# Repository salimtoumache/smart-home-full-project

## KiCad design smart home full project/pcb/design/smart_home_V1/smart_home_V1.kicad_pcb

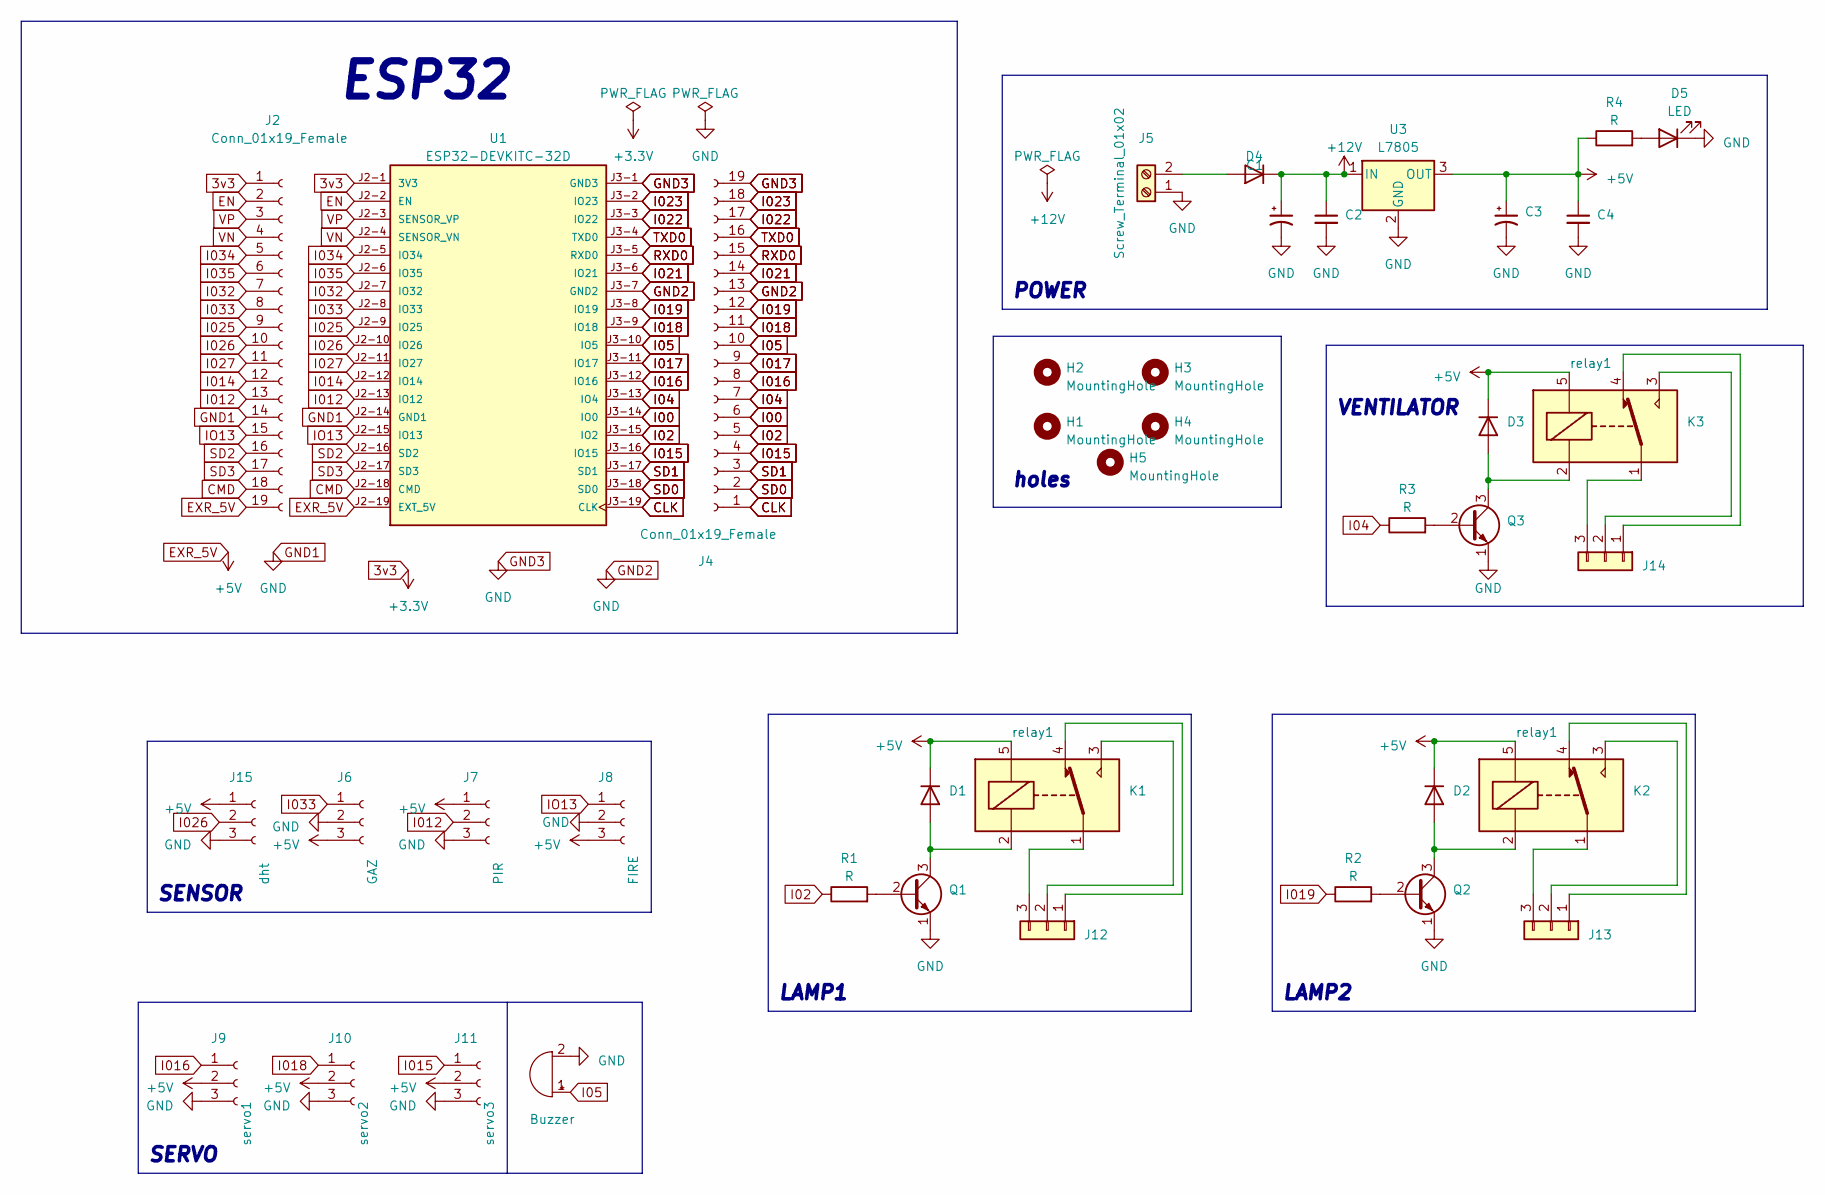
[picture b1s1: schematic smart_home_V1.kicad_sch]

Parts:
BZ1: Buzzer; MagneticBuzzer_ProSignal_ABI-010-RC
C1, C3: C_Polarized_Small_US; CP_Radial_D8.0mm_P3.50mm
C2, C4: C_Small; C_Disc_D4.7mm_W2.5mm_P5.00mm
D1, D2, D3, D4: 1N4448; D_DO-35_SOD27_P7.62mm_Horizontal
D5: LED; LED_D4.0mm
H1, H2, H3, H4, H5: MountingHole; MountingHole_2.5mm_Pad_TopBottom
J2, J4: Conn_01x19_Female; PinHeader_1x19_P2.00mm_Vertical
J5: Screw_Terminal_01x02; TerminalBlock_Phoenix_MKDS-1,5-2_1x02_P5.00mm_Horizontal
J6: GAZ; PinSocket_1x03_P2.54mm_Vertical
J7: PIR; PinSocket_1x03_P2.54mm_Vertical
J8: FIRE; PinSocket_1x03_P2.54mm_Vertical
J9: servo1; PinHeader_1x03_P2.54mm_Vertical
J10: servo2; PinHeader_1x03_P2.54mm_Vertical
J11: servo3; PinHeader_1x03_P2.54mm_Vertical
J12, J13, J14: Conn_01x03; TerminalBlock_Phoenix_MKDS-1,5-3-5.08_1x03_P5.08mm_Horizont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
J15: dht; PinSocket_1x03_P2.54mm_Vertical
K1, K2, K3: relay1; Relay_SPDT_SANYOU_SRD_Series_Form_C
Q1, Q2, Q3: 2N3904; TO-92_Inline
R1, R2, R3, R4: R; R_Axial_DIN0207_L6.3mm_D2.5mm_P7.62mm_Horizontal
U1: ESP32-DEVKITC-32D; MODULE_ESP32-DEVKITC-32D; PARTREV V4
U3: L7805; TO-220-3_Vertical

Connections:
3v3: J2.1, U1.J2-1 (3V3)
+12V: C1.1, C2.1, D4.1 (K), U3.1 (IN)
CLK: J4.1, U1.J3-19 (CLK)
CMD: J2.18, U1.J2-18 (CMD)
EN: J2.2, U1.J2-2 (EN)
EXR_5V: C3.1, C4.1, D1.1 (K), D2.1 (K), D3.1 (K), J2.19, J6.3, J7.1, J8.3, J9.2, J10.2, J11.2, J15.1, K1.5, K2.5, K3.5, R4.1, U1.J2-19 (EXT_5V), U3.3 (OUT)
GND1: BZ1.2 (+), C1.2, C2.2, C3.2, C4.2, D5.1 (K), J2.14, J4.13, J4.19, J5.1, J6.2, J7.3, J8.2, J9.3, J10.3, J11.3, J15.3, Q1.1 (E), Q2.1 (E), Q3.1 (E), U1.J2-14 (GND1), U1.J3-1 (GND3), U1.J3-7 (GND2), U3.2 (GND)
I00: J4.6, U1.J3-14 (IO0)
I02: J4.5, R1.1, U1.J3-15 (IO2)
I04: J4.7, R3.1, U1.J3-13 (IO4)
I05: BZ1.1 (-), J4.10, U1.J3-10 (IO5)
I012: J2.13, J7.2, U1.J2-13 (IO12)
I014: J2.12, U1.J2-12 (IO14)
I015: J4.4, J11.1, U1.J3-16 (IO15)
I016: J4.8, J9.1, U1.J3-12 (IO16)
I017: J4.9, U1.J3-11 (IO17)
I018: J4.11, J10.1, U1.J3-9 (IO18)
I019: J4.12, R2.1, U1.J3-8 (IO19)
I021: J4.14, U1.J3-6 (IO21)
I022: J4.17, U1.J3-3 (IO22)
I023: J4.18, U1.J3-2 (IO23)
I025: J2.9, U1.J2-9 (IO25)
I026: J2.10, J15.2, U1.J2-10 (IO26)
I027: J2.11, U1.J2-11 (IO27)
I032: J2.7, U1.J2-7 (IO32)
I033: J2.8, J6.1, U1.J2-8 (IO33)
I034: J2.5, U1.J2-5 (IO34)
I035: J2.6, U1.J2-6 (IO35)
IO13: J2.15, J8.1, U1.J2-15 (IO13)
unnamed: D1.2 (A), K1.2, Q1.3 (C)
unnamed: D2.2 (A), K2.2, Q2.3 (C)
unnamed: D3.2 (A), K3.2, Q3.3 (C)
unnamed: D4.2 (A), J5.2
unnamed: D5.2 (A), R4.2
unnamed: J12.1, K1.4
unnamed: J12.2, K1.3
unnamed: J12.3, K1.1
unnamed: J13.1, K2.4
unnamed: J13.2, K2.3
unnamed: J13.3, K2.1
unnamed: J14.1, K3.4
unnamed: J14.2, K3.3
unnamed: J14.3, K3.1
unnamed: Q1.2 (B), R1.2
unnamed: Q2.2 (B), R2.2
unnamed: Q3.2 (B), R3.2
RXD0: J4.15, U1.J3-5 (RXD0)
SD0: J4.2, U1.J3-18 (SD0)
SD1: J4.3, U1.J3-17 (SD1)
SD2: J2.16, U1.J2-16 (SD2)
SD3: J2.17, U1.J2-17 (SD3)
TXD0: J4.16, U1.J3-4 (TXD0)
VN: J2.4, U1.J2-4 (SENSOR_VN)
VP: J2.3, U1.J2-3 (SENSOR_VP)

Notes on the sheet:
SERVO
LAMP2
POWER
VENTILATOR
ESP32
LAMP1
holes
SENSOR

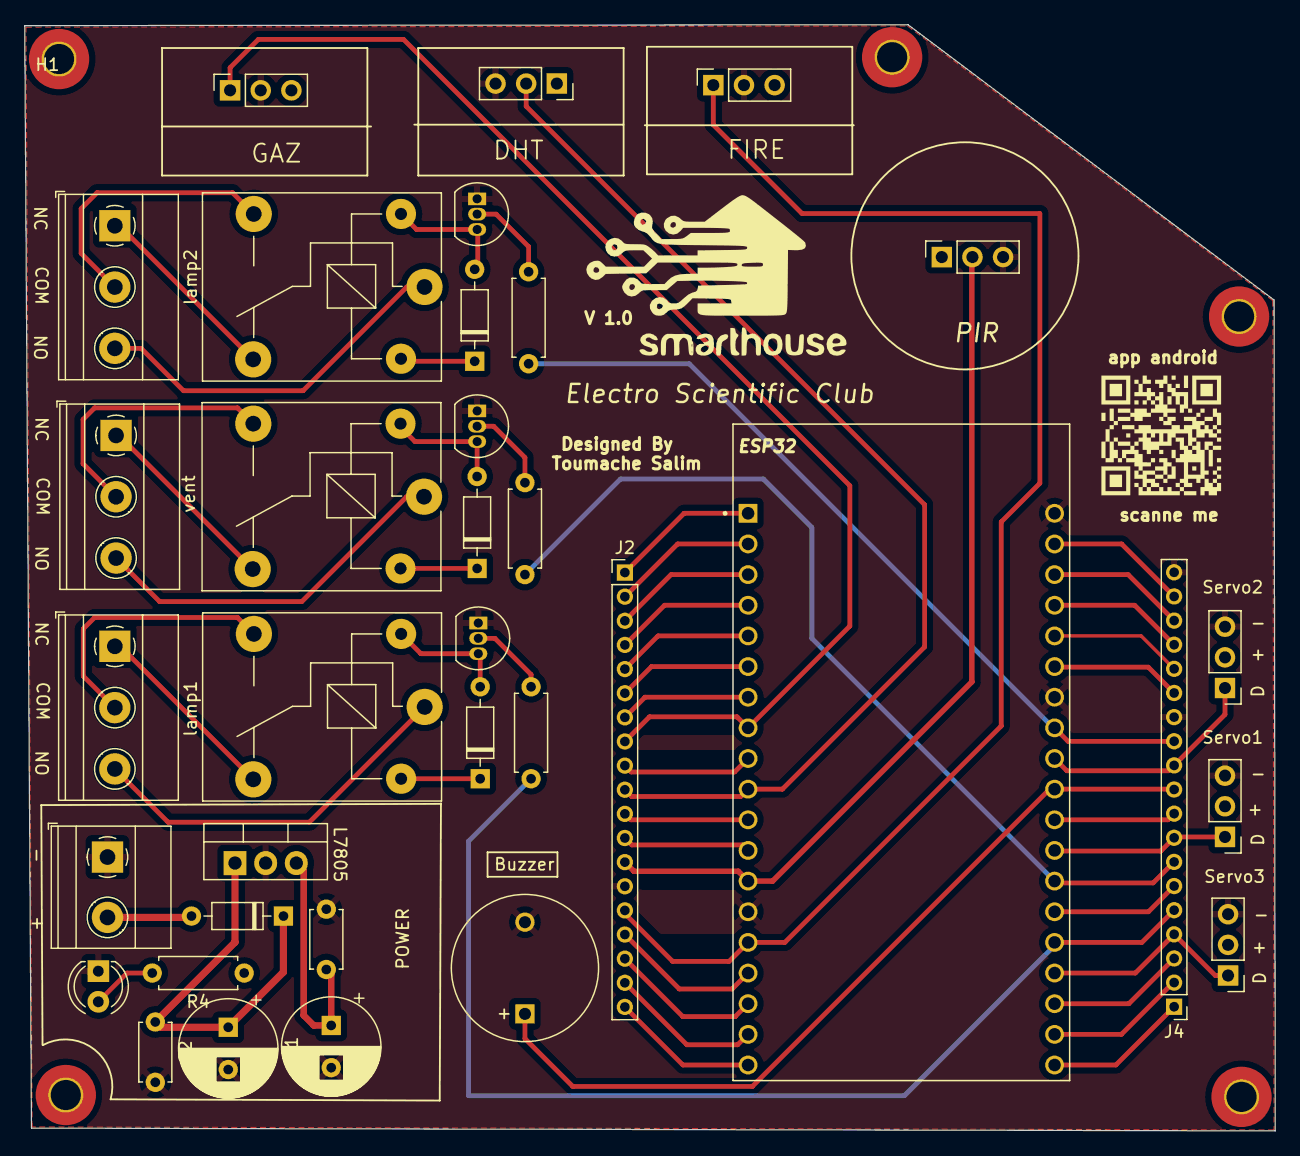
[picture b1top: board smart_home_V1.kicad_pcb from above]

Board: 2 copper layers, 103.6 x 91.7 mm, 40 parts (0 on the bottom side), 54 nets.
